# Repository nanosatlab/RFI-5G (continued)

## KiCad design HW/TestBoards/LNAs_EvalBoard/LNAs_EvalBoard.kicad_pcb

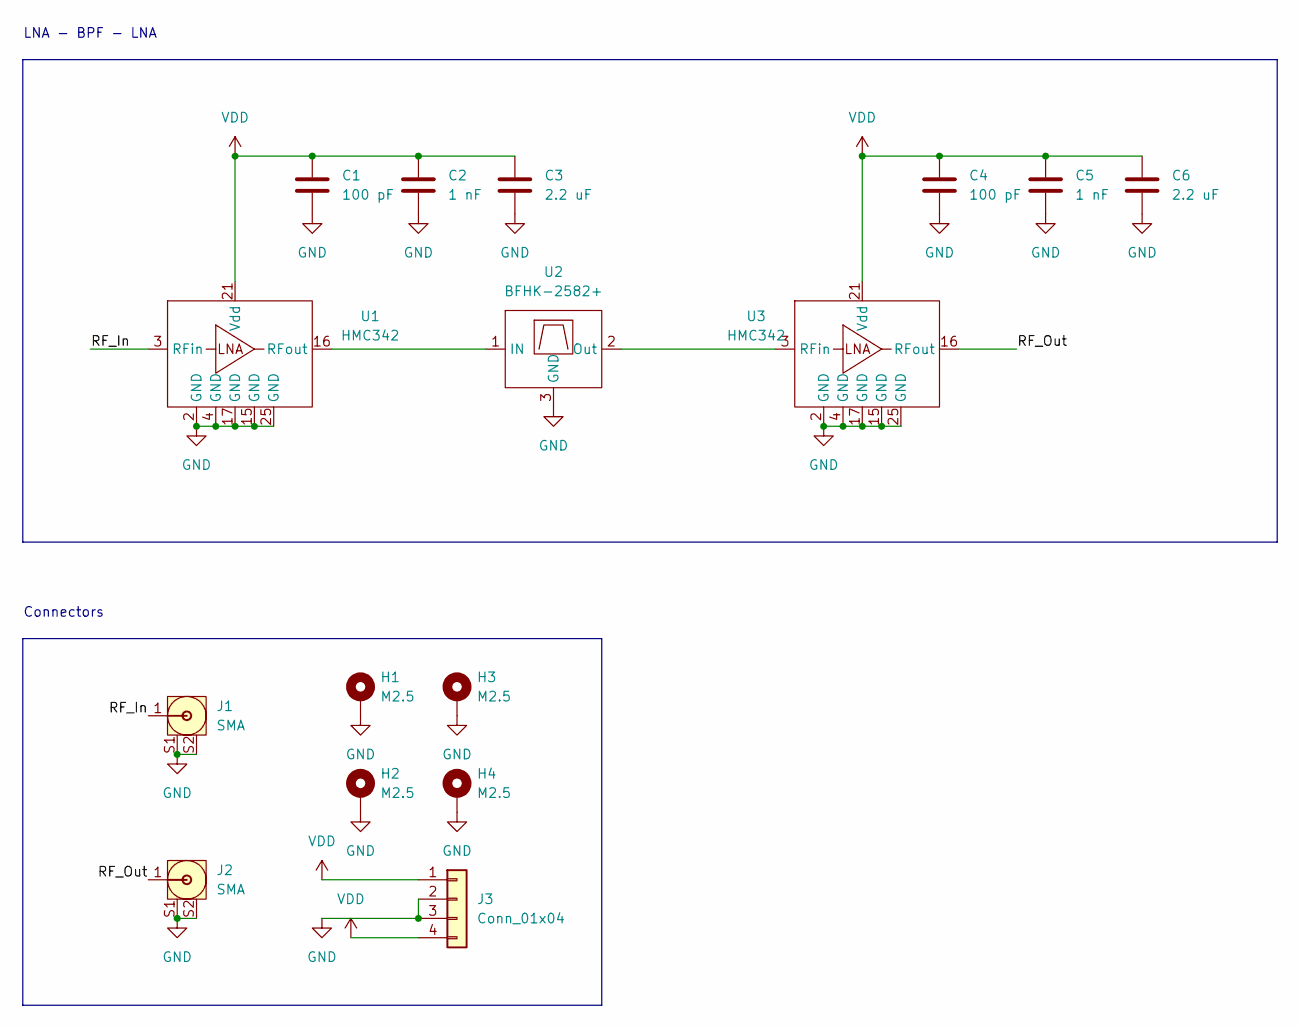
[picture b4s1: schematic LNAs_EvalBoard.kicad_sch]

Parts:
C1, C4: 100 pF; C_0603_1608Metric
C2, C5: 1 nF; C_0603_1608Metric
C3, C6: 2.2 uF; C_0603_1608Metric
H1, H2, H3, H4: M2.5; MountingHole_2.7mm_M2.5_Pad
J1, J2: SMA; Johnson_142-0761-861
J3: Conn_01x04; PinSocket_1x04_P2.00mm_Vertical
U1, U3: HMC342; QFN-24-1EP_4x4mm_P0.5mm_EP2.6x2.6mm
U2: BFHK-2582+; NM1812C-2

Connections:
/RF_In: J1.1, U1.3 (RFin)
/RF_Out: J2.1, U3.16 (RFout)
GND: C1.2, C2.2, C3.2, C4.2, C5.2, C6.2, H1.1, H2.1, H3.1, H4.1, J1.S1, J1.S2, J2.S1, J2.S2, J3.2, J3.3, U1.2 (GND), U1.4 (GND), U1.15 (GND), U1.17 (GND), U1.25 (GND), U2.3 (GND), U3.2 (GND), U3.4 (GND), U3.15 (GND), U3.17 (GND), U3.25 (GND)
unnamed: U1.16 (RFout), U2.1 (IN)
unnamed: U2.2 (Out), U3.3 (RFin)
VDD: C1.1, C2.1, C3.1, C4.1, C5.1, C6.1, J3.1, J3.4, U1.21 (Vdd), U3.21 (Vdd)

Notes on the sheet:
Connectors
LNA - BPF - LNA

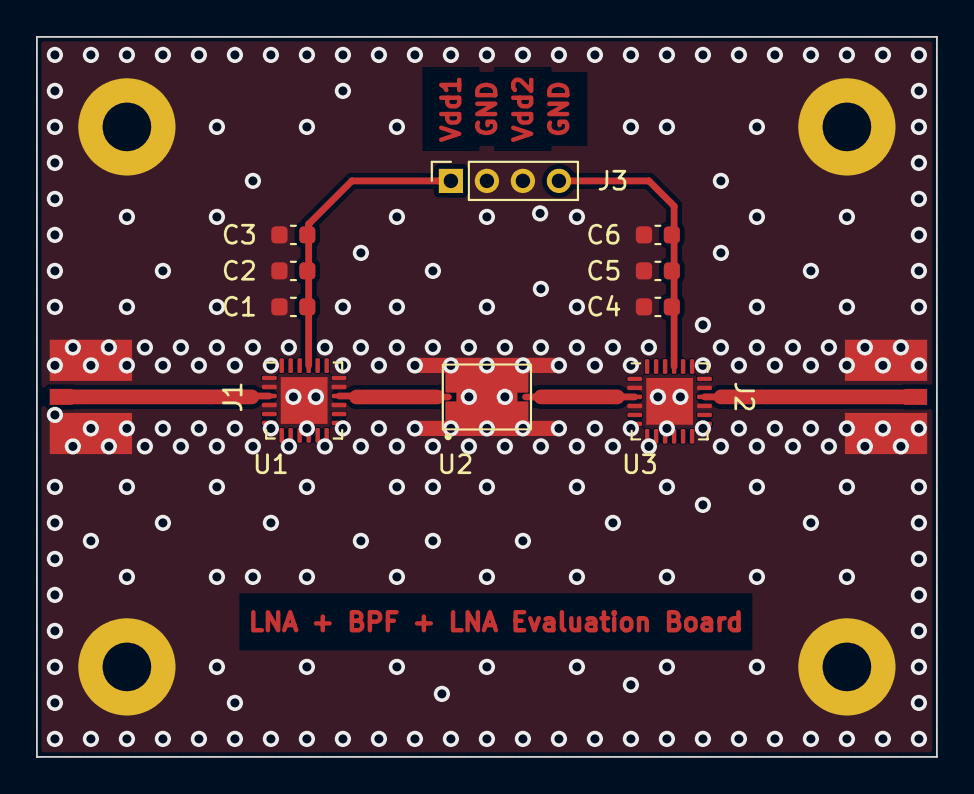
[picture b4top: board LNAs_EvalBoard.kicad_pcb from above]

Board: 2 copper layers, 50.0 x 40.0 mm, 16 parts (0 on the bottom side), 6 nets.

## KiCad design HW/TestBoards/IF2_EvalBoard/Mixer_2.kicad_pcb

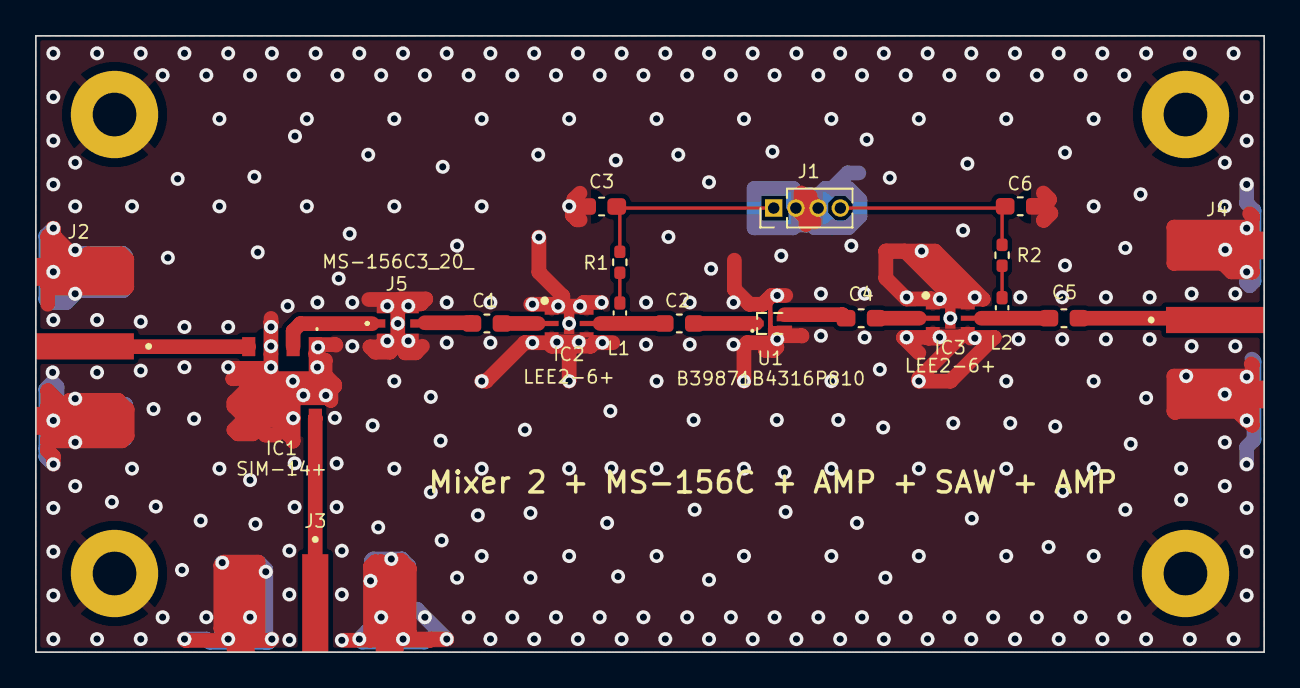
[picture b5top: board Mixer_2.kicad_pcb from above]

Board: 2 copper layers, 70.2 x 35.2 mm, 23 parts (0 on the bottom side), 16 nets.

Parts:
C1, C2, C4, C5: 2400 pF; C_0603_1608Metric_Pad1.08x0.95mm_HandSolder
C3, C6: 0.1 uF; C_0603_1608Metric_Pad1.08x0.95mm_HandSolder
H1, H2, H3, H4: M2.5; MountingHole_2.5mm_Pad
IC1: SIM-14+; SIM14
IC2, IC3: LEE2-6+; SON65P200X200X105-7N
J1: Conn_01x04; PinHeader_1x04_P1.27mm_Vertical
J2, J3, J4: SMA; LINX_CONSMA020.062-G
J5: MS-156C3_20_; MS156C320
L1, L2: 120 nH; L_0402_1005Metric_Pad0.77x0.64mm_HandSolder
R1, R2: 88.7; R_0402_1005Metric_Pad0.72x0.64mm_HandSolder
U1: B39871B4316P810

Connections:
/DC1: L1.1, R1.2
/DC2: L2.1, R2.2
/IF: IC1.2 (IF), J5.1 (COMMON)
/LO: IC1.8 (LO), J3.1 (RF)
/MS_out: C1.1, J5.3 (ANTENNA)
/RF: IC1.4 (RF), J2.1 (RF)
/RF_out: C5.2, J4.1 (RF)
/SAW_in: C2.2, U1.1 (IN)
/SAW_out: C4.1, U1.4 (OUT)
/Vdd_amp1: C3.2, J1.1, R1.1
/Vdd_amp2: C6.2, J1.4, R2.1
/amp1_in: C1.2, IC2.2 (RF-IN)
/amp1_out: C2.1, IC2.5 (RF-OUT&_DC-IN), L1.2
/amp2_in: C4.2, IC3.2 (RF-IN)
/amp2_out: C5.1, IC3.5 (RF-OUT&_DC-IN), L2.2
GND: C3.1, C6.1, H1.1, H2.1, H3.1, H4.1, IC1.1 (GROUND_1), IC1.3 (GROUND_2), IC1.5 (GROUND_3), IC1.6 (GROUND_4), IC1.7 (GROUND_5), IC1.9 (GROUND_6), IC1.10 (GROUND_7), IC2.1 (NC_1), IC2.3 (NC_2), IC2.4 (NC_3), IC2.6 (NC_4), IC2.7 (GND), IC3.1 (NC_1), IC3.3 (NC_2), IC3.4 (NC_3), IC3.6 (NC_4), IC3.7 (GND), J1.2, J1.3, J2.S1, J2.S2, J2.S3, J2.S4, J3.S1, J3.S2, J3.S3, J3.S4, J4.S1, J4.S2, J4.S3, J4.S4, J5.2 (GND_1), J5.4 (GND_2), J5.5 (GND_3), J5.6 (GND_4), J5.7 (GND_5), J5.8 (GND_6), U1.2 (GND), U1.3 (GND), U1.5 (GND)

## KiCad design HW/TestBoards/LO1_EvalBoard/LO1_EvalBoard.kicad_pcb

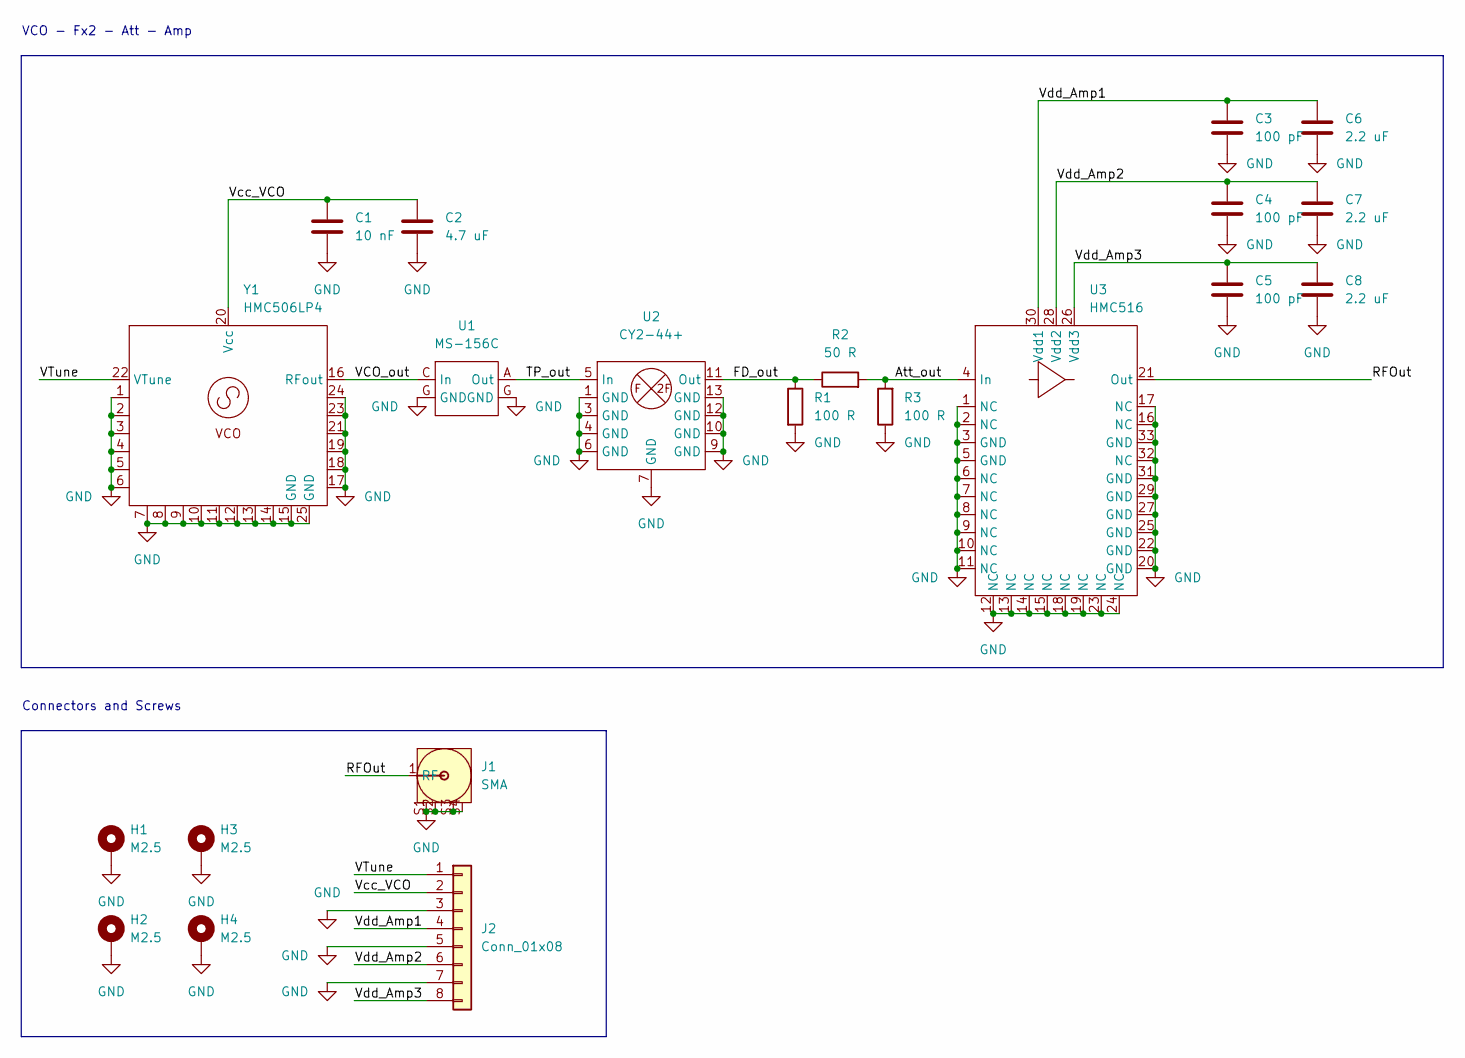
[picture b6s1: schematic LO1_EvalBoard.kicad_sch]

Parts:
C1: 10 nF; C_0603_1608Metric
C2: 4.7 uF; C_0603_1608Metric
C3, C4, C5: 100 pF; C_0603_1608Metric
C6, C7, C8: 2.2 uF; C_0603_1608Metric
H1, H2, H3, H4: M2.5; MountingHole_2.7mm_M2.5_Pad
J1: SMA; LINX_CONSMA020.062-G
J2: Conn_01x08; PinSocket_1x08_P2.00mm_Vertical
R1, R3: 100 R; R_0603_1608Metric
R2: 50 R; R_0603_1608Metric
U1: MS-156C; CoaxialSwitch_Hirose_MS-156C3_Horizontal
U2: CY2-44+; QFN-12-1EP_3x3mm_P0.5mm_EP1.65x1.65mm
U3: HMC516; QFN-32-1EP_5x5mm_P0.5mm_EP3.6x3.6mm
Y1: HMC506LP4; QFN-24-1EP_4x4mm_P0.5mm_EP2.7x2.7mm

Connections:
/Att_out: R2.2, R3.2, U3.4 (In)
/FD_out: R1.1, R2.1, U2.11 (Out)
/RFOut: J1.1 (RF), U3.21 (Out)
/TP_out: U1.A (Out), U2.5 (In); also elsewhere on the board
/VCO_out: U1.C (In), Y1.16 (RFout); also elsewhere on the board
/VTune: J2.1, Y1.22 (VTune)
/Vcc_VCO: C1.1, C2.1, J2.2, Y1.20 (Vcc)
/Vdd_Amp1: C3.1, C6.1, J2.4, U3.30 (Vdd1)
/Vdd_Amp2: C4.1, C7.1, J2.6, U3.28 (Vdd2)
/Vdd_Amp3: C5.1, C8.1, J2.8, U3.26 (Vdd3)
GND: C1.2, C2.2, C3.2, C4.2, C5.2, C6.2, C7.2, C8.2, H1.1, H2.1, H3.1, H4.1, J1.S1, J1.S2, J1.S3, J1.S4, J2.3, J2.5, J2.7, R1.2, R3.1, U1.G (GND), U2.1 (GND), U2.3 (GND), U2.4 (GND), U2.6 (GND), U2.7 (GND), U2.9 (GND), U2.10 (GND), U2.12 (GND), U2.13 (GND), U3.1 (NC), U3.2 (NC), U3.3 (GND), U3.5 (GND), U3.6 (NC), U3.7 (NC), U3.8 (NC), U3.9 (NC), U3.10 (NC), U3.11 (NC), U3.12 (NC), U3.13 (NC), U3.14 (NC), U3.15 (NC), U3.16 (NC), U3.17 (NC), U3.18 (NC), U3.19 (NC), U3.20 (GND), U3.22 (GND), U3.23 (NC), U3.24 (NC), U3.25 (GND), U3.27 (GND), U3.29 (GND), U3.31 (GND), U3.32 (NC), U3.33 (GND), Y1.1, Y1.2, Y1.3, Y1.4, Y1.5, Y1.6, Y1.7, Y1.8, Y1.9, Y1.10, Y1.11, Y1.12, Y1.13, Y1.14, Y1.15 (GND), Y1.17, Y1.18, Y1.19, Y1.21, Y1.23, Y1.24, Y1.25 (GND); also elsewhere on the board

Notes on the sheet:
Connectors and Screws
VCO - Fx2 - Att - Amp

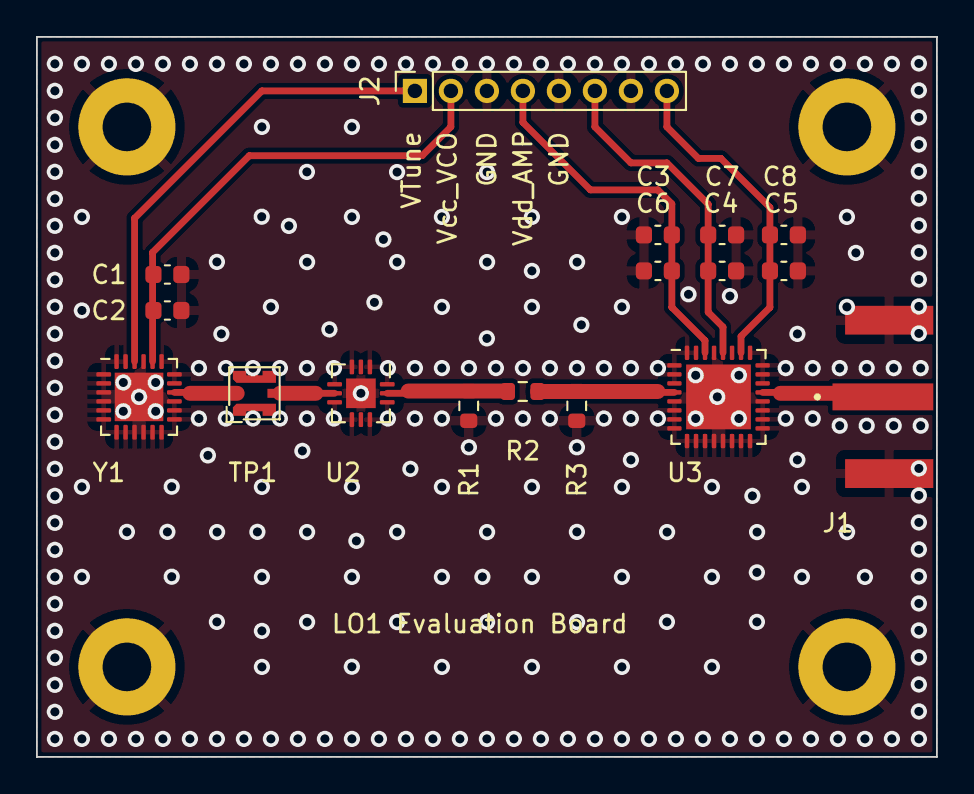
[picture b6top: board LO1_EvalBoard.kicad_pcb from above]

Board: 2 copper layers, 50.0 x 40.0 mm, 21 parts (0 on the bottom side), 11 nets.

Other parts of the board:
TP1: MS-156C; CoaxialSwitch_Hirose_MS-156C3_Horizontal

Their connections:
/TP_out: TP1.A (Out); also elsewhere on the board
/VCO_out: TP1.C (In); also elsewhere on the board
GND: TP1.G (GND); also elsewhere on the board

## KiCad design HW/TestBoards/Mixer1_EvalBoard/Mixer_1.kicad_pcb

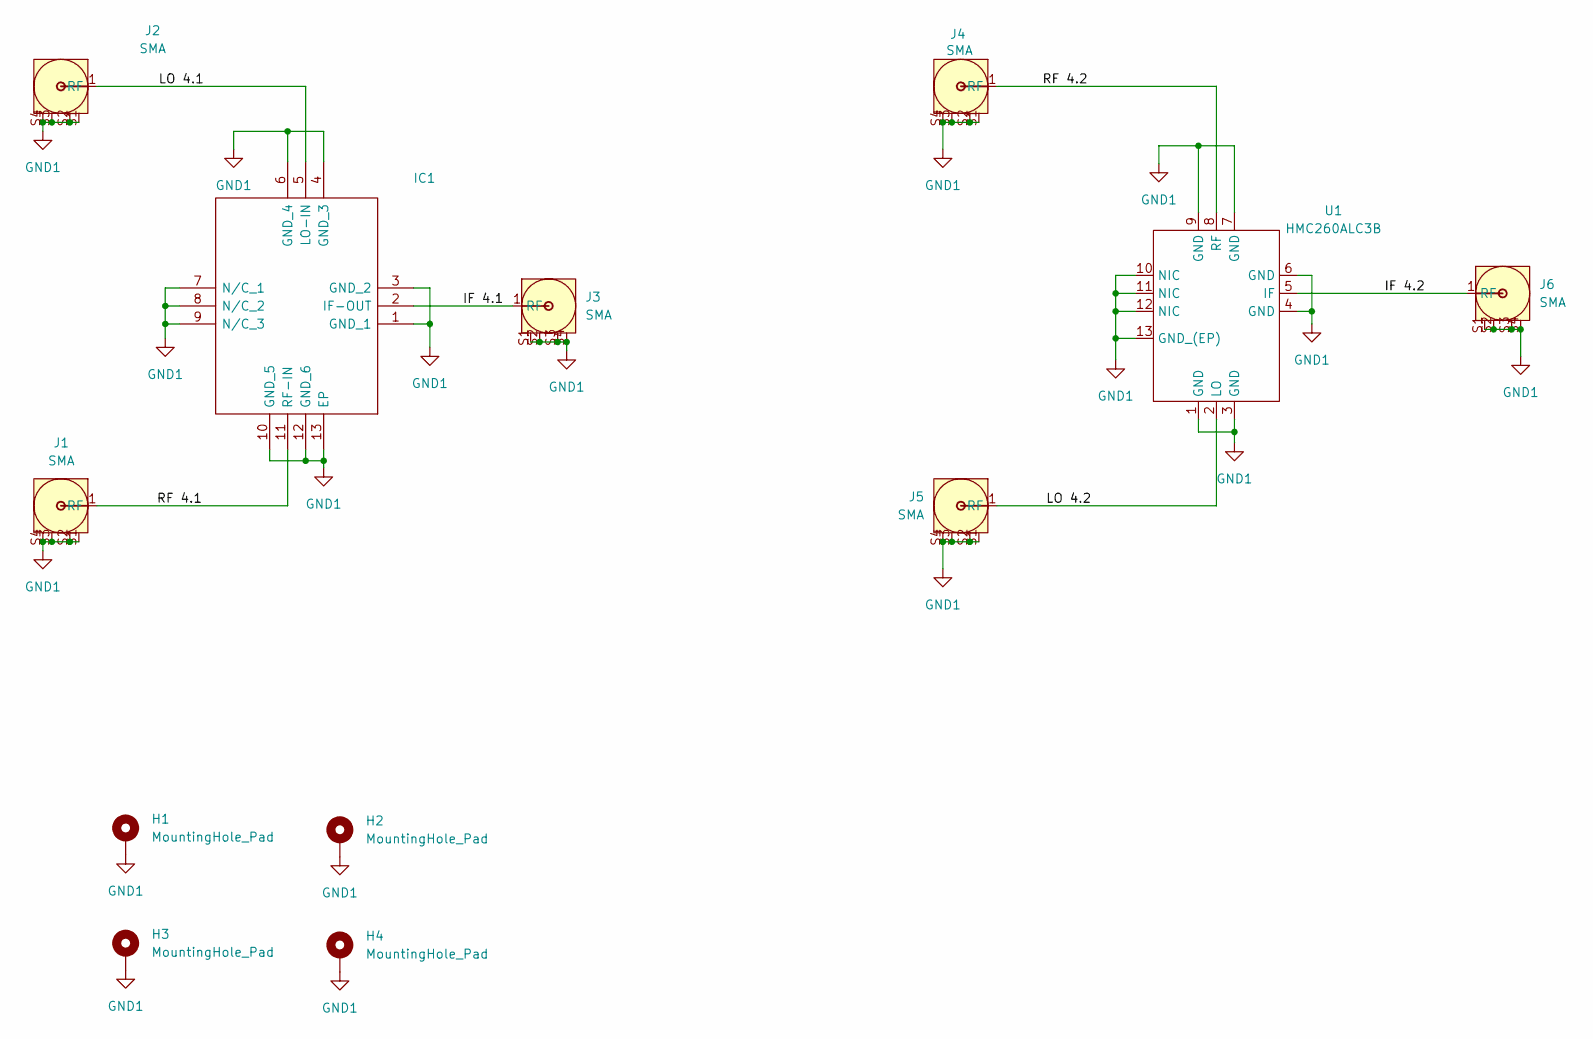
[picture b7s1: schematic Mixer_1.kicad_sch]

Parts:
H1, H2, H3, H4: MountingHole_Pad; MountingHole_2.5mm_Pad
IC1: QFN51P300X300X89-13N; Mouser Part Number 139-MDB-44H
J1, J2, J3, J4, J5, J6: SMA; LINX_CONSMA020.062-G
U1: HMC260ALC3B

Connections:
/IF 4.1: IC1.2 (IF-OUT), J3.1 (RF)
/IF 4.2: J6.1 (RF), U1.5 (IF)
/LO 4.1: IC1.5 (LO-IN), J2.1 (RF)
/LO 4.2: J5.1 (RF), U1.2 (LO)
/RF 4.1: IC1.11 (RF-IN), J1.1 (RF)
/RF 4.2: J4.1 (RF), U1.8 (RF)
GND1: H1.1, H2.1, H3.1, H4.1, IC1.1 (GND_1), IC1.3 (GND_2), IC1.4 (GND_3), IC1.6 (GND_4), IC1.7 (N/C_1), IC1.8 (N/C_2), IC1.9 (N/C_3), IC1.10 (GND_5), IC1.12 (GND_6), IC1.13 (EP), J1.S1, J1.S2, J1.S3, J1.S4, J2.S1, J2.S2, J2.S3, J2.S4, J3.S1, J3.S2, J3.S3, J3.S4, J4.S1, J4.S2, J4.S3, J4.S4, J5.S1, J5.S2, J5.S3, J5.S4, J6.S1, J6.S2, J6.S3, J6.S4, U1.1 (GND), U1.3 (GND), U1.4 (GND), U1.6 (GND), U1.7 (GND), U1.9 (GND), U1.10 (NIC), U1.11 (NIC), U1.12 (NIC), U1.13 (GND_(EP))

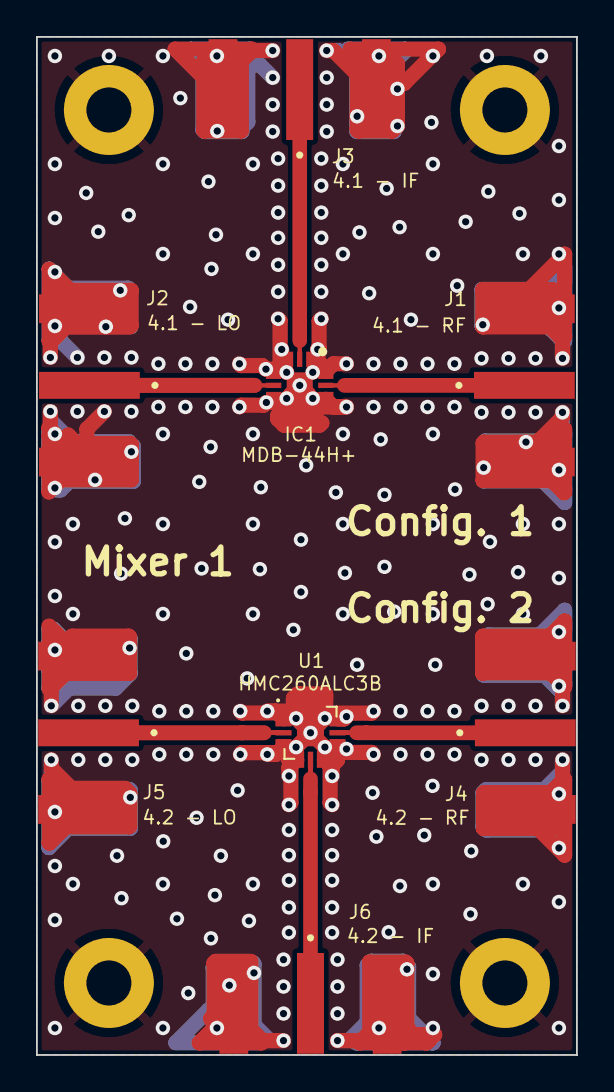
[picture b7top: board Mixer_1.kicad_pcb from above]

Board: 2 copper layers, 30.0 x 56.6 mm, 12 parts (0 on the bottom side), 7 nets.

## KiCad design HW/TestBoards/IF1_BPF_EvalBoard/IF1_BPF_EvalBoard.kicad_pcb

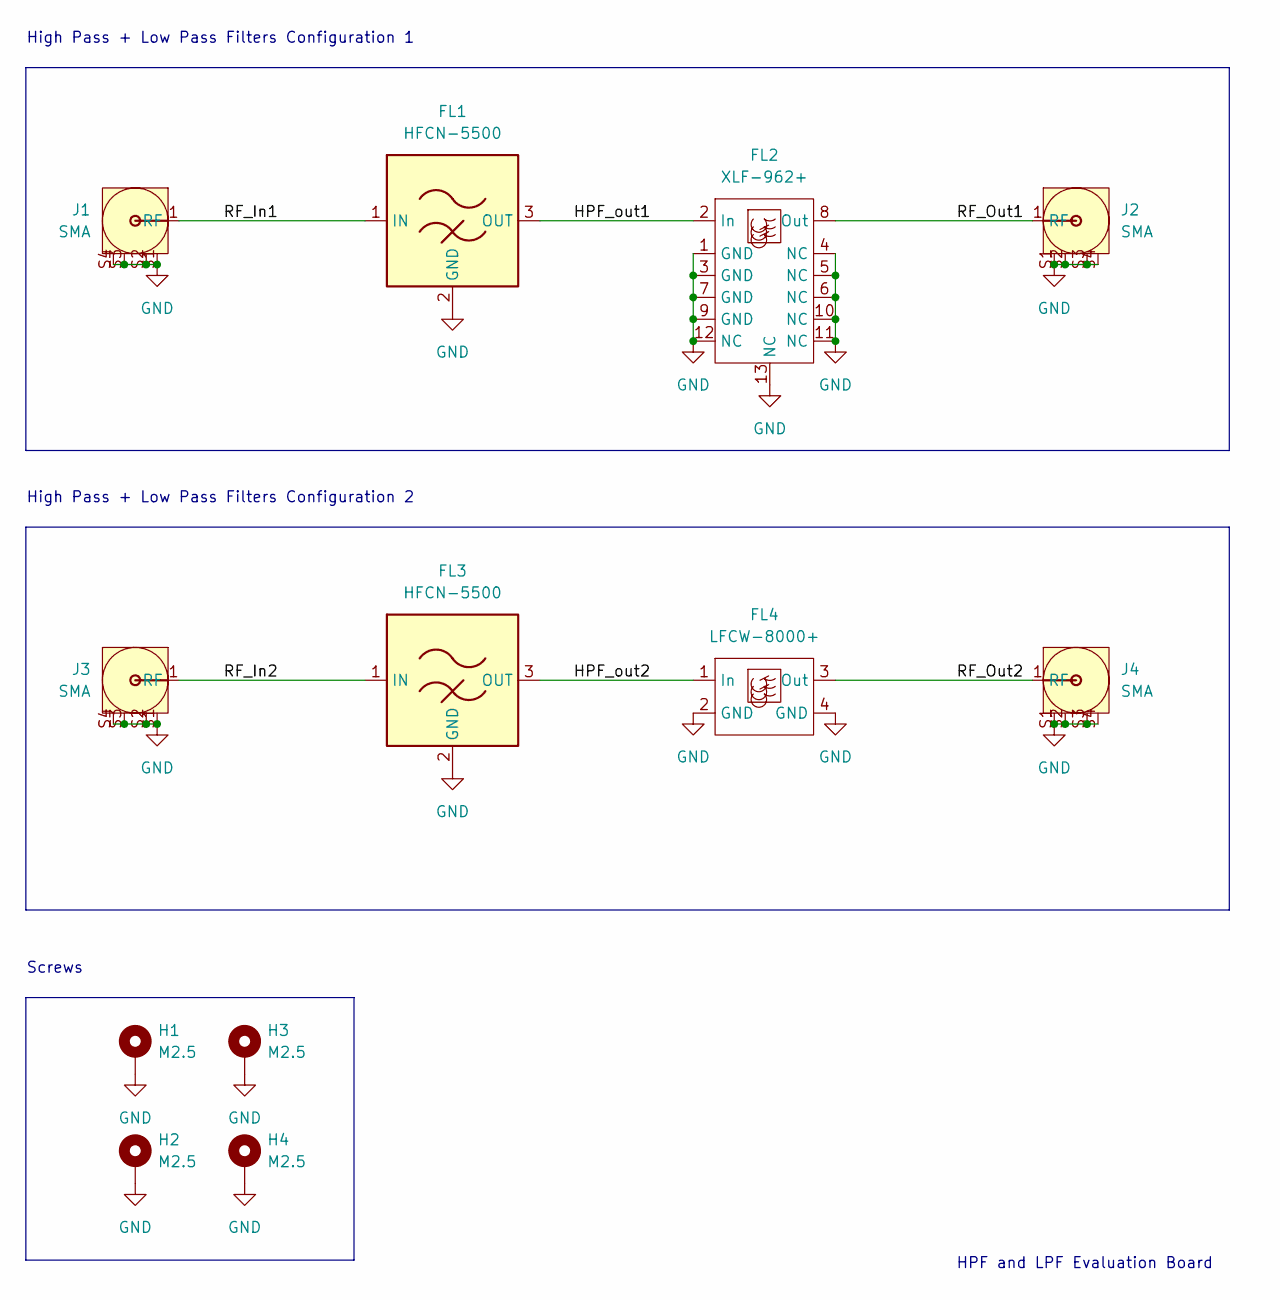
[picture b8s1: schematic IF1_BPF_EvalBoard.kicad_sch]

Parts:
FL1, FL3: HFCN-5500; Filter_Mini-Circuits_FV1206-1
FL2: XLF-962+; QFN-12-1EP_3x3mm_P0.51mm_EP1.45x1.45mm
FL4: LFCW-8000+; JC0603C-1
H1, H2, H3, H4: M2.5; MountingHole_2.7mm_M2.5_Pad
J1, J2, J3, J4: SMA; LINX_CONSMA020.062-G

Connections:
/HPF_out1: FL1.3 (OUT), FL2.2 (In)
/HPF_out2: FL3.3 (OUT), FL4.1 (In)
/RF_In1: FL1.1 (IN), J1.1 (RF)
/RF_In2: FL3.1 (IN), J3.1 (RF)
/RF_Out1: FL2.8 (Out), J2.1 (RF)
/RF_Out2: FL4.3 (Out), J4.1 (RF)
GND: FL1.2 (GND), FL1.4 (GND), FL1.5 (GND), FL1.6 (GND), FL2.1 (GND), FL2.3 (GND), FL2.4 (NC), FL2.5 (NC), FL2.6 (NC), FL2.7 (GND), FL2.9 (GND), FL2.10 (NC), FL2.11 (NC), FL2.12 (NC), FL2.13 (NC), FL3.2 (GND), FL3.4 (GND), FL3.5 (GND), FL3.6 (GND), FL4.2 (GND), FL4.4 (GND), H1.1, H2.1, H3.1, H4.1, J1.S1, J1.S2, J1.S3, J1.S4, J2.S1, J2.S2, J2.S3, J2.S4, J3.S1, J3.S2, J3.S3, J3.S4, J4.S1, J4.S2, J4.S3, J4.S4

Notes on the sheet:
High Pass + Low Pass Filters Configuration 2
HPF and LPF Evaluation Board
High Pass + Low Pass Filters Configuration 1
Screws

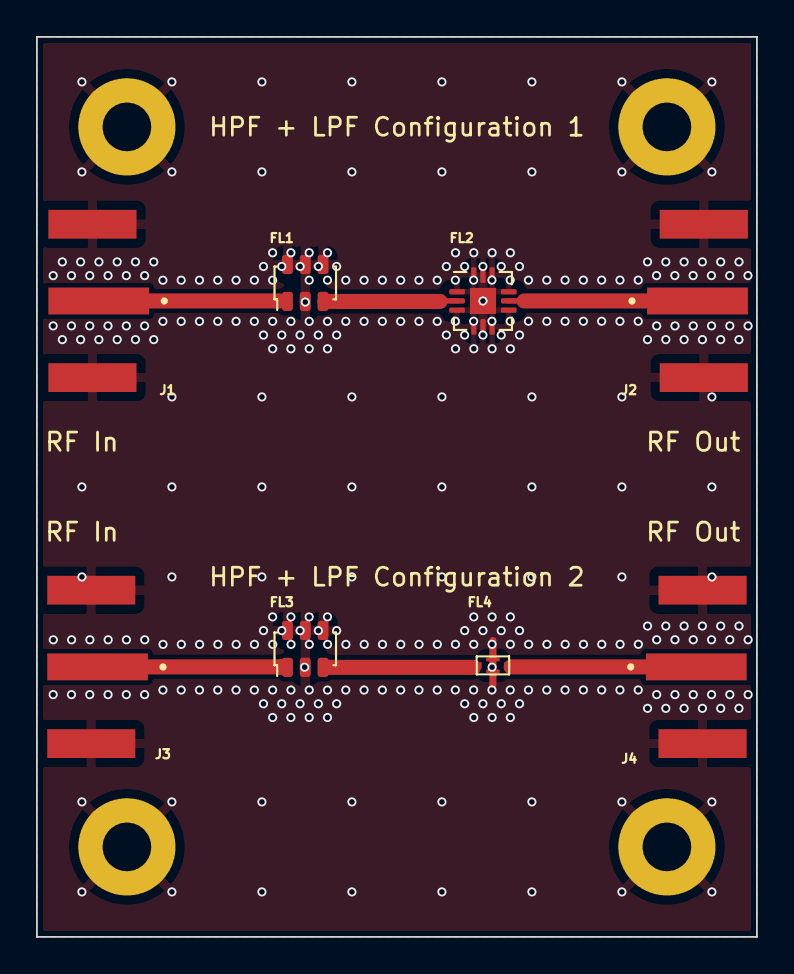
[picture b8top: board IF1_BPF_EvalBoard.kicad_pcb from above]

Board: 2 copper layers, 40.0 x 50.0 mm, 12 parts (0 on the bottom side), 7 nets.

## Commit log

2022-03-21 HPF and LPF EvalBoard
2022-03-22 LNAs_EvalBoard
2022-03-22 LNA Eval Board
2022-03-23 LO1 Eval Board
2022-03-31 All Test Boards developed
2022-04-07 Added Evaluation Boards for RO4003C 1.52 mm
2022-04-12 EvalBoards in RO4003C 60 mils
2022-06-10 Boards started
2022-06-15 RF top and Bottom boards
2022-06-21 PL boards
2022-07-15 All boards dseigned, thickness change pending
2022-08-02 almost finished PCB's
